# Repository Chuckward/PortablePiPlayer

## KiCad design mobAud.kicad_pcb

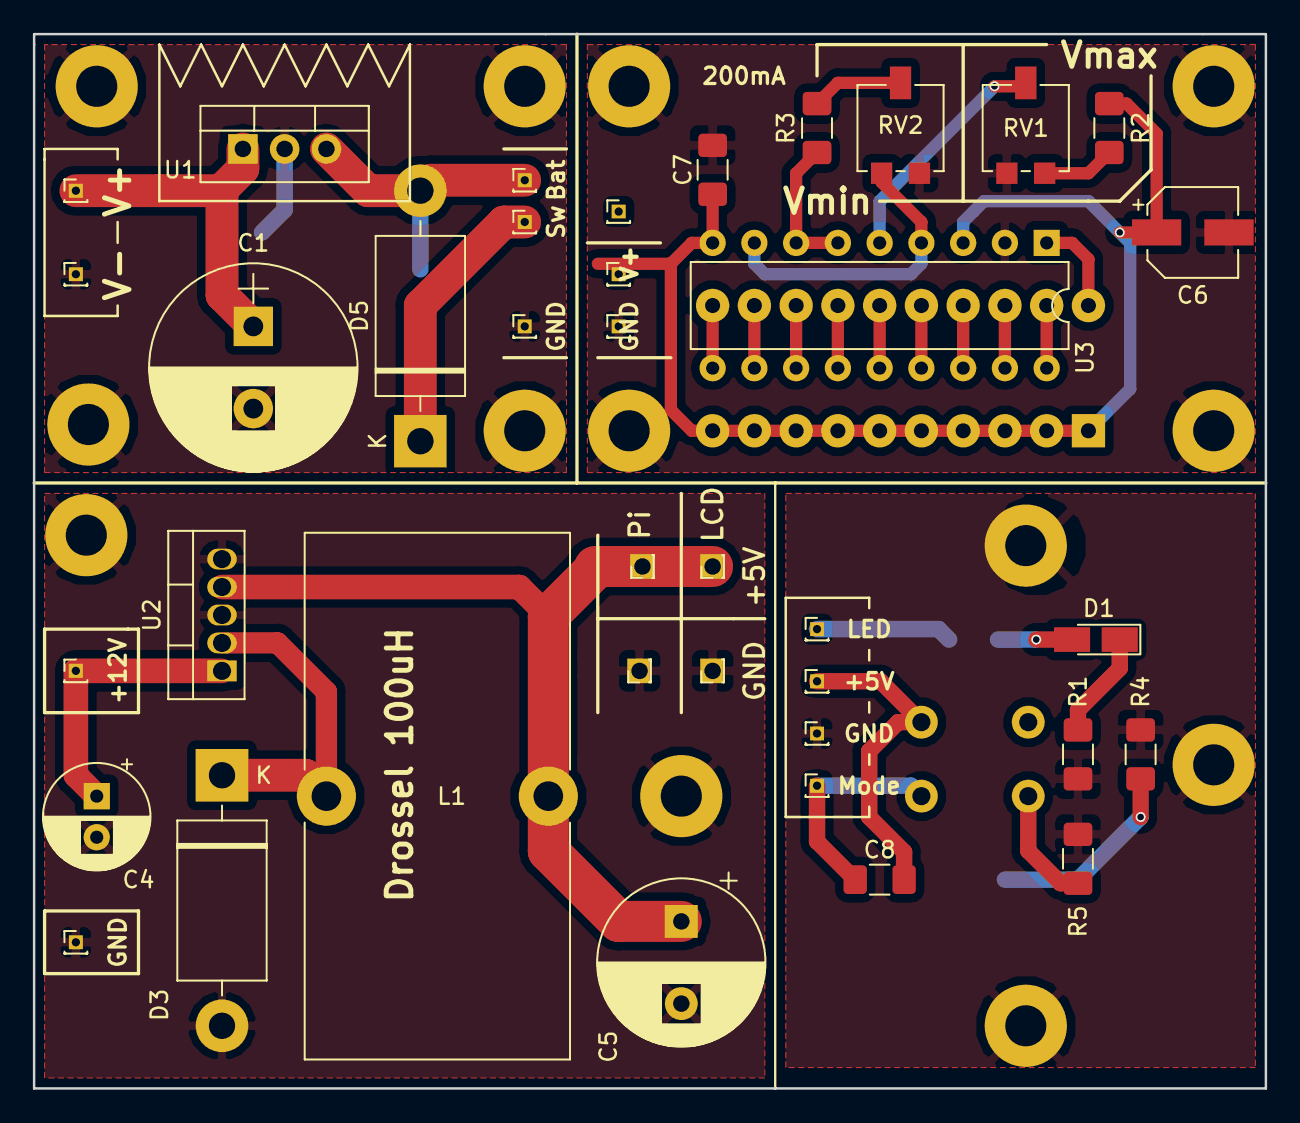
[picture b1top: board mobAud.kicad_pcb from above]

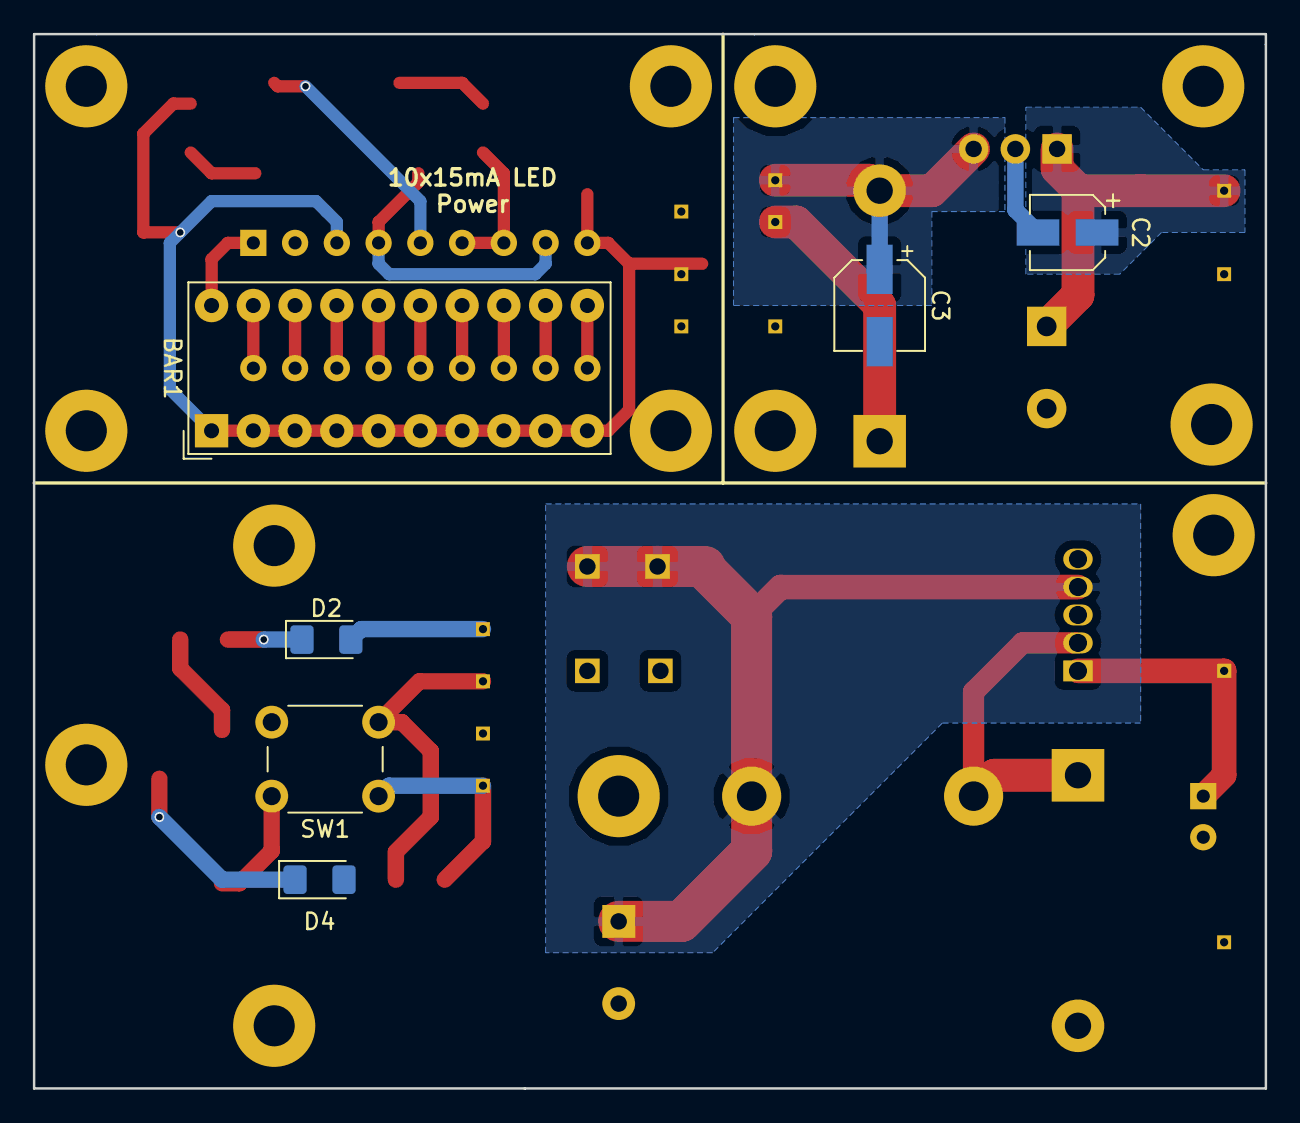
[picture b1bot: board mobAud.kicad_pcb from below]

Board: 2 copper layers, 74.9 x 64.1 mm, 57 parts (6 on the bottom side), 33 nets.

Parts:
BAR1: HDSP-4830_2; HDSP-4830
C1: 1000u; CP_Radial_D12.5mm_P5.00mm
C2: 1u; CP_Elec_4x5.3
C3, C6: 10u; CP_Elec_5x5.4
C4: 100u; CP_Radial_D6.3mm_P2.50mm
C5: 1000u; CP_Radial_D10.0mm_P5.00mm
C7: 0.1u; C_1206_3216Metric_Pad1.42x1.75mm_HandSolder
C8: 100n; C_1206_3216Metric_Pad1.42x1.75mm_HandSolder
CON1, CON4, CON6, CON12: SW; PinHeader_1x01_P1.00mm_Vertical
CON2, CON10: Bat-; PinHeader_1x01_P1.00mm_Vertical
CON3: Bat+; PinHeader_1x01_P1.00mm_Vertical
CON5: GND; PinHeader_1x01_P1.00mm_Vertical
CON7: 5V LCD; PinHeader_1x01_P1.00mm_Vertical
CON8: GND PI; PinHeader_1x01_P1.00mm_Vertical
CON9: 5V PI; PinHeader_1x01_P1.00mm_Vertical
CON11: GND LCD; PinHeader_1x01_P1.00mm_Vertical
CON13: 5V; PinHeader_1x01_P1.00mm_Vertical
CON14: GND_S; PinHeader_1x01_P1.00mm_Vertical
CON16: Mode_Con; PinHeader_1x01_P1.00mm_Vertical
CON17: Mode; PinHeader_1x01_P1.00mm_Vertical
D1: 1N4148; D_MicroMELF_Hadsoldering
D2: LEDR; LED_1206_3216Metric_Pad1.42x1.75mm_HandSolder
D3: 1N5822; D_DO-201AD_P15.24mm_Horizontal
D4: LEDG; LED_1206_3216Metric_Pad1.42x1.75mm_HandSolder
D5: SB120; D_DO-201AD_P15.24mm_Horizontal
L1: L; L_Toroid_Vertical_L31.8mm_W15.9mm_P13.50mm_Bourns_5700
MK1, MK2, MK3, MK4, MK5, MK6, MK7, MK8, MK9, MK10, MK11, MK12, MK13: Mounting_Hole_PAD; MountingHole_2.5mm_Pad
R1: 5k6; R_1206_3216Metric_Pad1.42x1.75mm_HandSolder
R2: 4.7k; R_1206_3216Metric_Pad1.42x1.75mm_HandSolder
R3: 1.2k; R_1206_3216Metric_Pad1.42x1.75mm_HandSolder
R4: 180; R_1206_3216Metric_Pad1.42x1.75mm_HandSolder
R5: 10k; R_1206_3216Metric_Pad1.42x1.75mm_HandSolder
RV1, RV2: 4.7k; Potentiometer_Vishay_TS53YL_Vertical
SW1: SW_DPDT_x2; SW_PUSH_6mm_H5mm
U1: PB137; TO-220-3_Vertical
U2: LM2576HVS-5; TO-220-5_Vertical
U3: LM3914; DIP-18_W7.62mm
V+1: +18V; PinHeader_1x01_P1.00mm_Vertical
V-1: GND; PinHeader_1x01_P1.00mm_Vertical

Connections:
/5V_S: C8.2, CON13.1, D4.2, SW1.2
/5V_V: BAR1.1, BAR1.2, BAR1.3, BAR1.4, BAR1.5, BAR1.6, BAR1.7, BAR1.8, BAR1.9, BAR1.10, C6.1, C7.1, CON1.1, R2.2, U3.3
/+5: C5.1, CON7.1, CON9.1, L1.2, U2.4
/+12: C4.1, CON6.1, U2.1
/+12V: C3.1, CON3.1, D5.2, U1.3
/+18V: C1.1, C2.1, U1.1, V+1.1
/GND_5V: C4.2, C5.2, CON8.1, CON10.1, CON11.1, D3.2, MK5.1, MK6.1, U2.3, U2.5
/GND_S: CON14.1, MK11.1, MK12.1, MK13.1, R1.2, R4.2, R5.1
/GND_V: C6.2, C7.2, CON2.1, MK7.1, MK8.1, MK9.1, MK10.1, RV1.3, RV2.1, U3.2
GND: C1.2, C2.2, C3.2, CON5.1, MK1.1, MK2.1, MK3.1, MK4.1, U1.2, V-1.1
unnamed: BAR1.11, U3.10
unnamed: BAR1.12, U3.11
unnamed: BAR1.13, U3.12
unnamed: BAR1.14, U3.13
unnamed: BAR1.15, U3.14
unnamed: BAR1.16, U3.15
unnamed: BAR1.17, U3.16
unnamed: BAR1.18, U3.17
unnamed: BAR1.19, U3.18
unnamed: BAR1.20, U3.1
unnamed: C8.1, CON16.1, R5.2, SW1.1
unnamed: CON4.1, D5.1
unnamed: CON12.1, D2.2
unnamed: CON17.1, U3.9
unnamed: D1.1, R1.1
unnamed: D1.2, D2.1
unnamed: D3.1, L1.1, U2.2
unnamed: D4.1, R4.1
unnamed: R2.1, RV1.1
unnamed: R3.1, RV2.2
unnamed: R3.2, U3.6, U3.7
unnamed: RV1.2, U3.5
unnamed: RV2.3, U3.4, U3.8

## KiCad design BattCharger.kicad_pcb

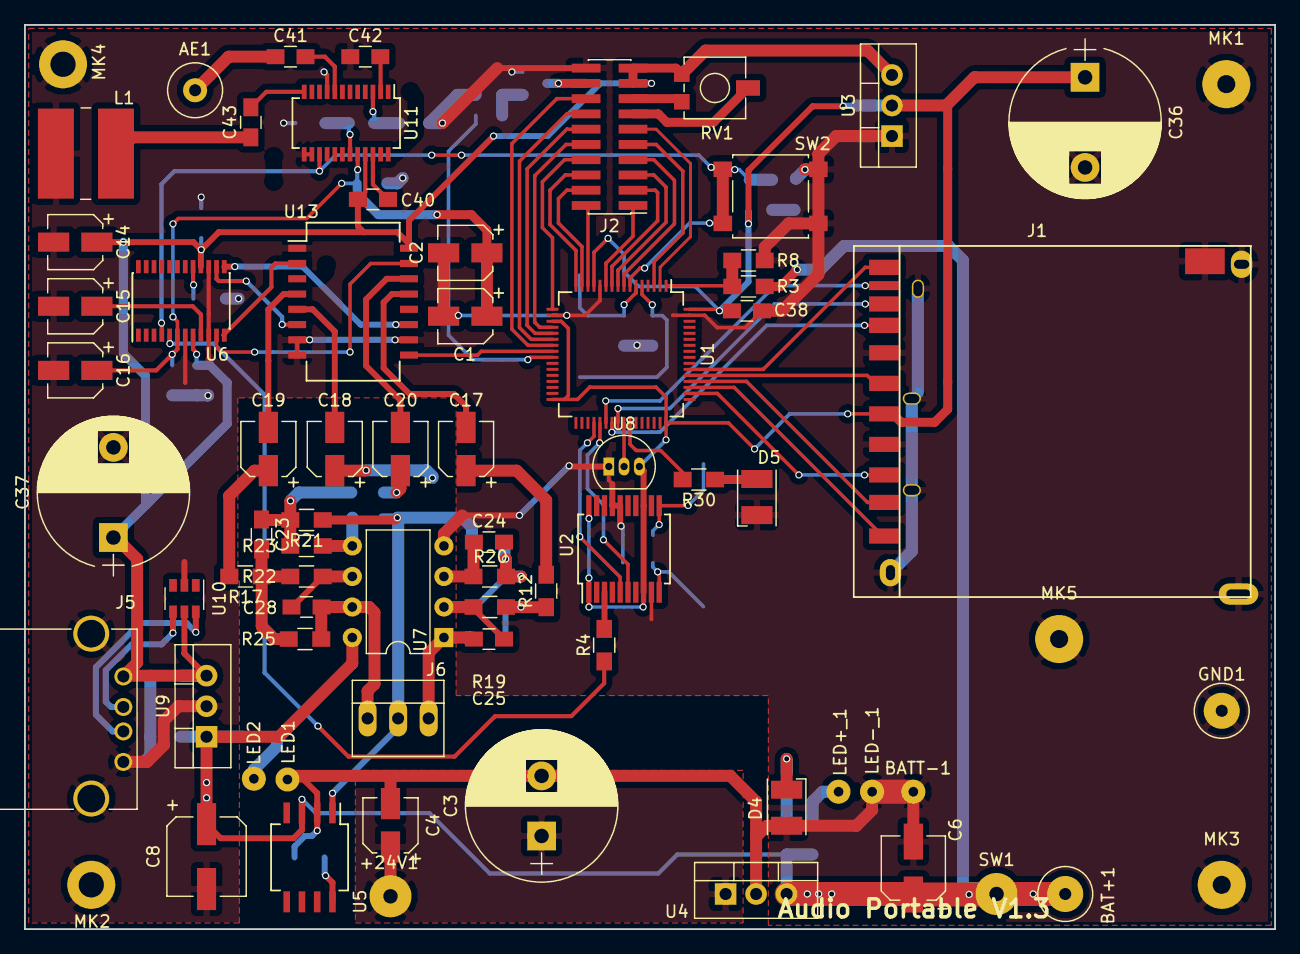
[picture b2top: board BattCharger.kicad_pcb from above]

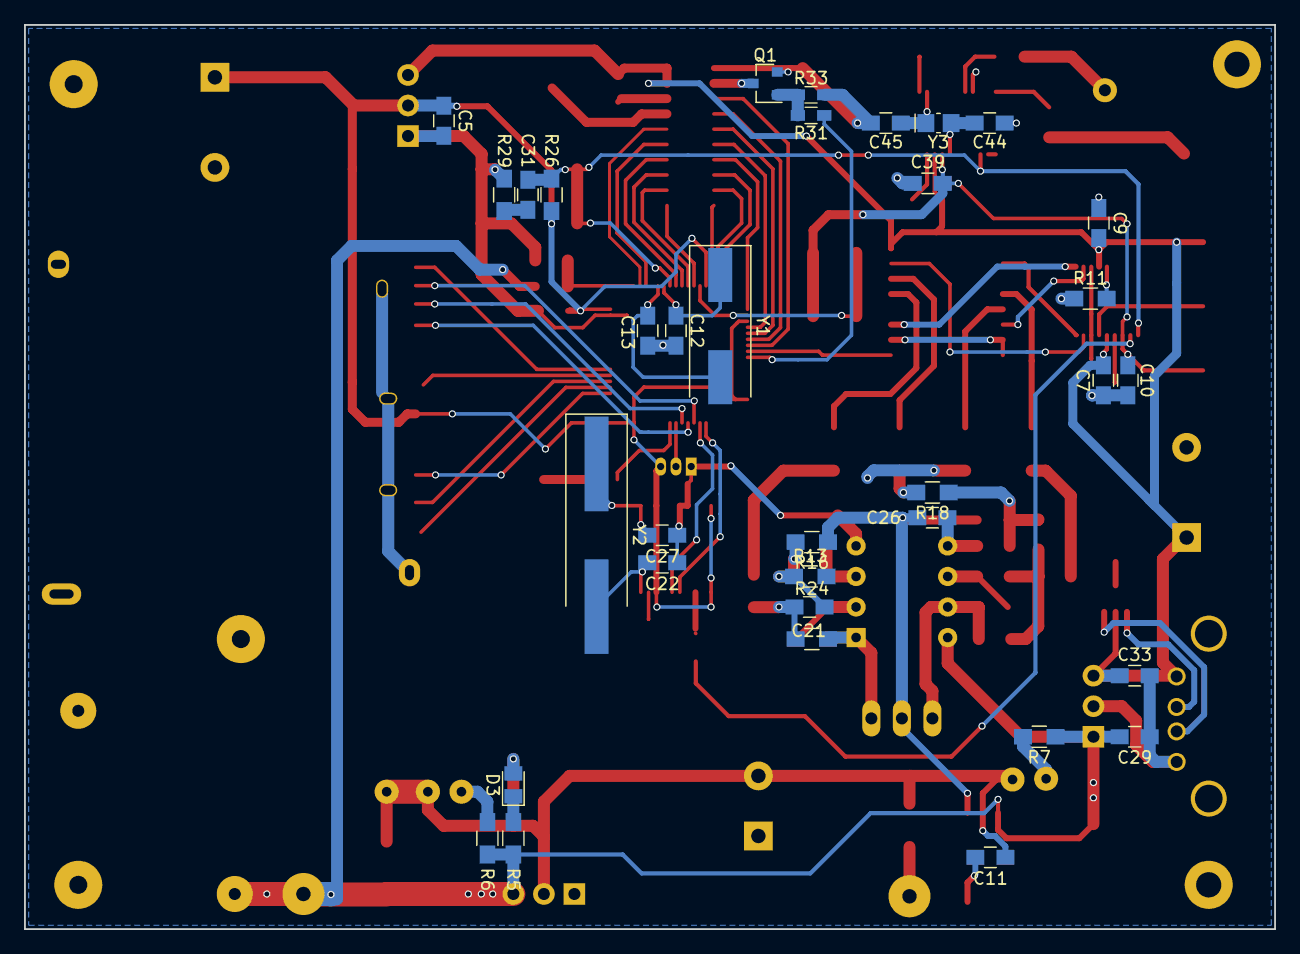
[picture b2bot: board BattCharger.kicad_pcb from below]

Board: 2 copper layers, 104.0 x 75.2 mm, 106 parts (34 on the bottom side), 93 nets.

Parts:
+24V1: +24V; SolderWirePad_single_1-2mmDrill
AE1: Antenna; 1pin
BAT+1: BAT+; 1pin
BATT-1: BAT-; SolderWirePad_single_0-8mmDrill
C1, C2, C17, C18, C19, C20: 10u; CP_Elec_4x5.8
C3: 1000u; CP_Radial_D12.5mm_P5.00mm
C4: 1u; CP_Elec_4x5.3
C5, C29, C31, C33, C38, C39: 100n; C_0805_HandSoldering
C6: 10u; CP_Elec_5x5.8
C7, C9, C10, C11: 1u; C_0805_HandSoldering
C8: 220u; CP_Elec_6.3x7.7
C12, C13, C22, C27, C44, C45: 22p; C_0805_HandSoldering
C14, C15, C16: 10u; CP_Elec_4x5.3
C21, C23: 3.3n; C_0805_HandSoldering
C24, C25, C26, C28, C40: 6.8n; C_0805_HandSoldering
C36, C37: 1000u; CP_Radial_D12.5mm_P7.50mm
C41: 1n; C_0805_HandSoldering
C42: 2.2p; C_0805_HandSoldering
C43: 0.47u; C_0805_HandSoldering
D3: 1N4148; D_MicroMELF
D4: LEDR; LED_PLCC-2
D5: LED_ERR; LED_PLCC-2
GND1: GND; 1pin
J1: SD_Card; SDCARD-REVERSE
J2: CONN_02X10; Pin_Header_Straight_2x10_Pitch1.27mm_SMD
J5: USB_A
J6: CONN_01X03; PINHEAD1-3
L1: Ferrite_Bead_Small; L_Wuerth_WE-PD2-Typ-L
LED1: LED2-; SolderWirePad_single_0-8mmDrill
LED2: LED2+; SolderWirePad_single_0-8mmDrill
LED+_1: LED+; SolderWirePad_single_0-8mmDrill
LED-_1: LED-; SolderWirePad_single_0-8mmDrill
MK1, MK2, MK3, MK4, MK5: Mounting_Hole_PAD; SolderWirePad_single_1-5mmDrill
Q1: BSS123; SOT-23
R3: 40k; R_0805_HandSoldering
R4: 100; R_0805_HandSoldering
R5, R6, R7: 5k6; R_0805_HandSoldering
R8, R11, R26: 10k; R_0805_HandSoldering
R12, R13, R17, R18: 7.5k; R_0805_HandSoldering
R16, R21, R24, R25: 5.6k; R_0805_HandSoldering
R19, R20, R22, R23: 360; R_0805_HandSoldering
R29: 120; R_0805_HandSoldering
R30: 750R; R_0805_HandSoldering
R31: 1k; R_0603_HandSoldering
R33: 9k; R_0603_HandSoldering
RV1: 10k; Potentiometer_Trimmer_Vishay_TS53YL
SW1: SW; SolderWirePad_single_1-2mmDrill
SW2: SW_DPST; SW_SPST_B3S-1000_alt
U1: STM32F205RBTx; LQFP-64_10x10mm_Pitch0.5mm
U2: PLL1707/1708; SSOP-20_5.3x7.2mm_Pitch0.65mm
U3: LD1117S33TR; TO-220-3_Vertical
U4: PB137; TO-220-3_Vertical
U5: TLE2426; SO-8_5.3x6.2mm_Pitch1.27mm
U6: PCM1789; TSSOP-24_4.4x7.8mm_Pitch0.65mm
U7: NE5532; DIP-8_W7.62mm
U8: DS1822; TO-92_Inline_Narrow_Oval
U9: LM7805CT; TO-220-3_Vertical
U10: USBLC6-2SC6; SOT-23-6
U11: Si4730-D60-GU; SSOP-24_3.9x8.7mm_Pitch0.635mm
U13: MC14551B; SOIC-16W_7.5x12.8mm_Pitch1.27mm
Y1: 20.000; Crystal_SMD_HC49-SD
Y2: 27.000; Crystal_SMD_HC49-SD_HandSoldering
Y3: 32.768k; Crystal_SMD_MicroCrystal_CC8V-T1A-2pin_2.0x1.2mm_HandSolder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

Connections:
6V+: BAT+1.1, C6.1, C8.1, C29.1, R3.1, R5.2, R6.1, R7.1, SW1.1, U4.3, U5.3, U7.8, U9.1
6V-: BATT-1.1, C1.2, C2.2, C3.2, C4.2, C5.2, C6.2, C7.1, C8.2, C9.1, C10.1, C11.1, C12.2, C13.2, C14.2, C15.2, C16.2, C22.1, C27.1, C29.2, C33.2, C36.2, C37.2, C38.1, C39.2, C42.1, C44.1, C45.1, D4.2, D5.1, GND1.1, J1.3, J1.6, J1.12, J1.13, J1.14, J1.15, J1.16, J1.17, J1.18, J2.20, J5.4, J5.5, L1.2, LED1.1, LED-_1.1, MK1.1, MK2.1, MK3.1, MK4.1, MK5.1, Q1.2, R8.1, R11.1, R29.1, R33.2, SW2.2, SW2.4, U1.12, U1.18, U1.63, U2.9, U2.16, U2.17, U3.1, U4.2, U5.2, U6.7, U6.10, U6.15, U7.4, U8.1, U9.2, U10.2, U11.9, U11.13, U11.14, U13.1, U13.7, U13.8, U13.10
+3V3: C1.1, C2.1, C5.1, C10.2, C16.1, C36.1, C38.2, C39.1, J1.4, R26.1, U1.13, U1.19, U1.32, U1.48, U1.64, U2.1, U2.8, U2.13, U2.20, U3.2, U6.6, U8.3, U11.20
+5V: C7.2, C9.2, C14.1, C33.1, C37.1, C40.1, J2.17, J2.19, J5.1, RV1.3, U3.3, U6.8, U6.16, U9.3, U10.5, U11.21, U13.16
/+24V: +24V1.1, C3.1, C4.1, U4.1
D0: J2.1, U1.11
D1: J2.2, U1.14
D2: J2.3, U1.10
D3: J2.4, U1.15
D4: J2.5, U1.9
D5: J2.6, U1.16
D6: J2.7, U1.8
D7: J2.8, U1.17
DFS: C42.2, U11.2
ERROR: R30.2, U1.42
FM_L: U11.24, U13.3
FM_R: U11.23, U13.12
FM_SCL: U1.61, U11.17
FM_SDIO: U1.62, U11.18
FREQ_SEL1: U1.36, U2.5
FREQ_SEL2: U1.37, U2.6
GLCD_L: R31.1, U1.25
GPIO3: C45.2, U11.3, Y3.1
K: J2.18, Q1.3
LCD_CS1: J2.12, U1.21
LCD_CS2: J2.14, U1.22
LCD_EN: J2.11, U1.2
LCD_RS: J2.9, U1.3
LCD_RST: J2.16, U1.23
LCD_RW: J2.10, U1.20
LEFT: C28.2, J6.1, R25.1, U7.7
MP3OUTL+: U6.12, U13.2
MP3OUTL-: U6.11, U13.15
MP3OUTR+: U6.13, U13.11
MP3OUTR-: U6.14, U13.6
MUX: U1.24, U13.9
unnamed: AE1.1, C41.1
unnamed: C11.2, U5.8
unnamed: C17.1, R12.2
unnamed: C18.1, R13.2
unnamed: C19.1, R17.2
unnamed: C20.1, R18.2
unnamed: C21.1, R13.1, R16.2, R20.2
unnamed: C21.2, R12.1, R19.2, R24.2
unnamed: C23.1, R18.1, R21.2, R23.2
unnamed: C23.2, R17.1, R22.2, R25.2
unnamed: C24.1, R20.1, U7.3
unnamed: C25.1, R19.1, U7.2
unnamed: C26.1, R23.1, U7.5
unnamed: C28.1, R22.1, U7.6
unnamed: C31.2, R29.2
unnamed: C40.2, U11.22
unnamed: C41.2, U11.8
unnamed: C43.1, L1.1
unnamed: C43.2, U11.12
unnamed: D3.1, R5.1
unnamed: D3.2, D4.1
unnamed: D5.2, R30.1
unnamed: LED2.1, R7.2
unnamed: LED+_1.1, R6.2
unnamed: Q1.1, R31.2, R33.1
unnamed: R3.2, R8.2, U1.1
unnamed: R4.2, U2.3
unnamed: R11.2, U6.17
PLL_XT1: C22.2, U2.10, Y2.2
PLL_XT2: C27.2, U2.11, Y2.1
RCLK: C44.2, U11.19, Y3.2
RESET: C31.1, R26.2, SW2.1, SW2.3, U1.7, U6.4, U11.15
RIGHT: C25.2, J6.3, R24.1, U7.1
SCKI: R4.1, U6.5
SD_CD: J1.10, U1.38
SD_CLK: J1.5, U1.53
SD_CMD: J1.2, U1.50
SD_D0: J1.7, U1.39
SD_D1: J1.8, U1.40
SD_D2: J1.9, U1.51
SD_D3: J1.1, U1.52
SD_WP: J1.11, U1.54
TEMP: U1.41, U8.2
USB_D+: J5.3, U10.6
USB_D+IC: U1.45, U10.1
USB_D-: J5.2, U10.4
USB_D-IC: U1.44, U10.3
V0: J2.13, RV1.2
VCOM: C15.1, U6.9
VEE: J2.15, RV1.1
VGND: C24.2, C26.2, J6.2, R16.1, R21.1, U5.1
VOUTL+: C19.2, U13.4
VOUTL-: C20.2, U13.14
VOUTR+: C17.2, U13.13
VOUTR-: C18.2, U13.5
XTAL1: C12.1, U1.6, Y1.1
XTAL2: C13.1, U1.5, Y1.2

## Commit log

2018-08-14 Added schematics, pcb and net as-is
2018-08-21 modified circuit diagram and board
